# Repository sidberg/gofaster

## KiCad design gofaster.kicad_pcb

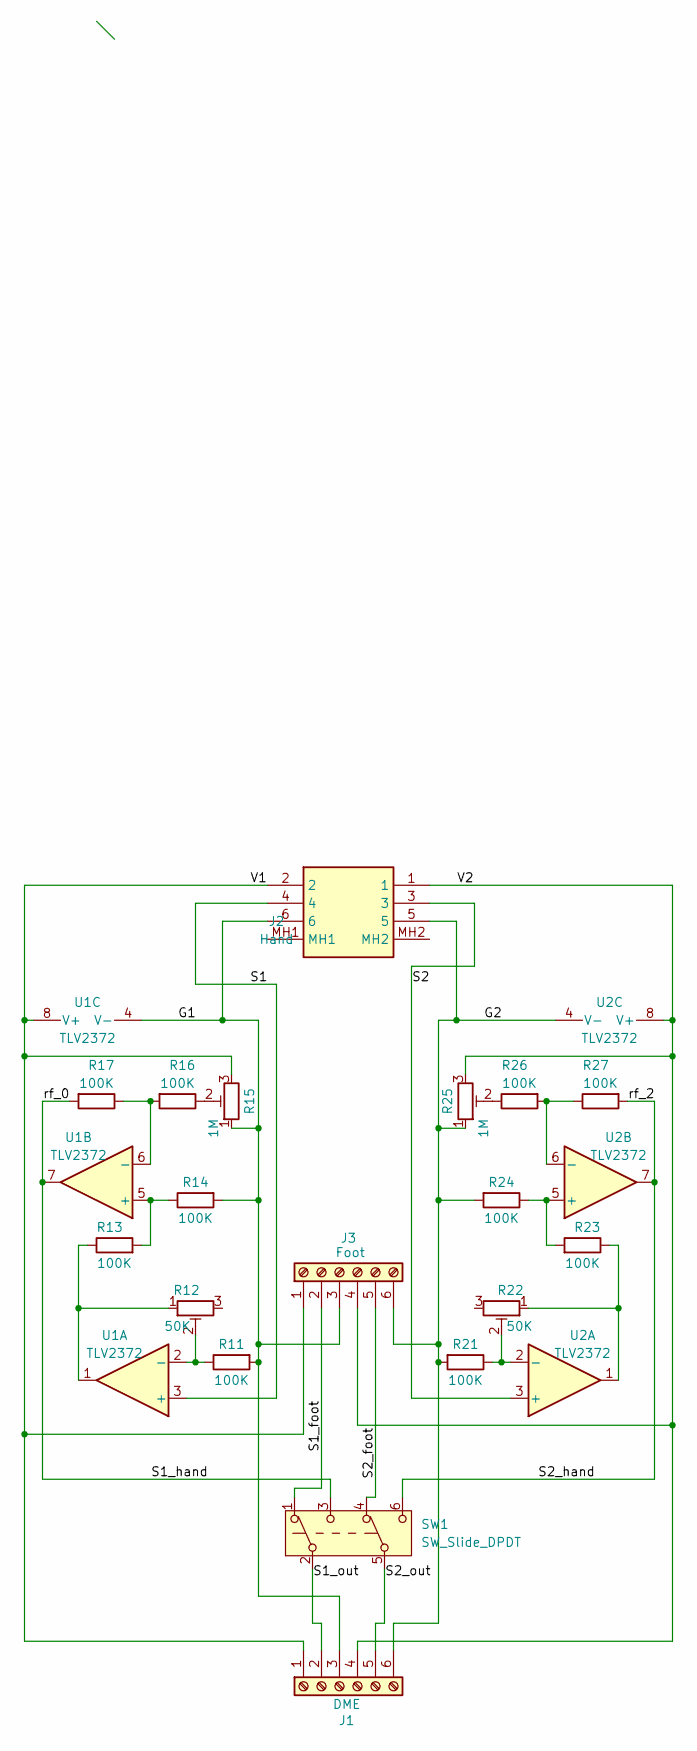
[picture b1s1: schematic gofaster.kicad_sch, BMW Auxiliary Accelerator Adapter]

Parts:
J1: DME; CUI_TB002-500-06BE
J2: Hand; 39294069; Mouser Part Number 538-39-29-4069
J3: Foot; CUI_TB002-500-06BE
R11, R13, R14, R16, R17, R21, R23, R24, R26, R27: 100K; R_Axial_DIN0207_L6.3mm_D2.5mm_P7.62mm_Horizontal
R12, R22: 50K; Potentiometer_Bourns_3339S_Horizontal
R15, R25: 1M; Potentiometer_Bourns_3339S_Horizontal
SW1: SW_Slide_DPDT; PBH2UEEKZXNAG1RBLK
U1, U2: TLV2372; DIP-8_W7.62mm

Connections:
/G1: J1.3, J2.6, J3.3, R11.2, R14.2, R15.1, U1.4 (V-)
/G2: J1.6, J2.5, J3.6, R21.2, R24.2, R25.1, U2.4 (V-)
/S1: J2.4, U1.3 (+)
/S1_foot: J3.2, SW1.1 (A)
/S1_hand: R17.2, SW1.3 (C), U1.7
/S1_out: J1.2, SW1.2 (B)
/S2: J2.3, U2.3 (+)
/S2_foot: J3.5, SW1.4 (A)
/S2_hand: R27.2, SW1.6 (C), U2.7
/S2_out: J1.5, SW1.5 (B)
/V1: J1.1, J2.2, J3.1, R15.3, U1.8 (V+)
/V2: J1.4, J2.1, J3.4, R25.3, U2.8 (V+)
unnamed: R12.1, R13.1, U1.1
unnamed: R15.2, R16.1
unnamed: R22.1, R23.1, U2.1
unnamed: R25.2, R26.1
unnamed: R11.1, R12.2, U1.2 (-)
unnamed: R13.2, R14.1, U1.5 (+)
unnamed: R16.2, R17.1, U1.6 (-)
unnamed: R21.1, R22.2, U2.2 (-)
unnamed: R23.2, R24.1, U2.5 (+)
unnamed: R26.2, R27.1, U2.6 (-)

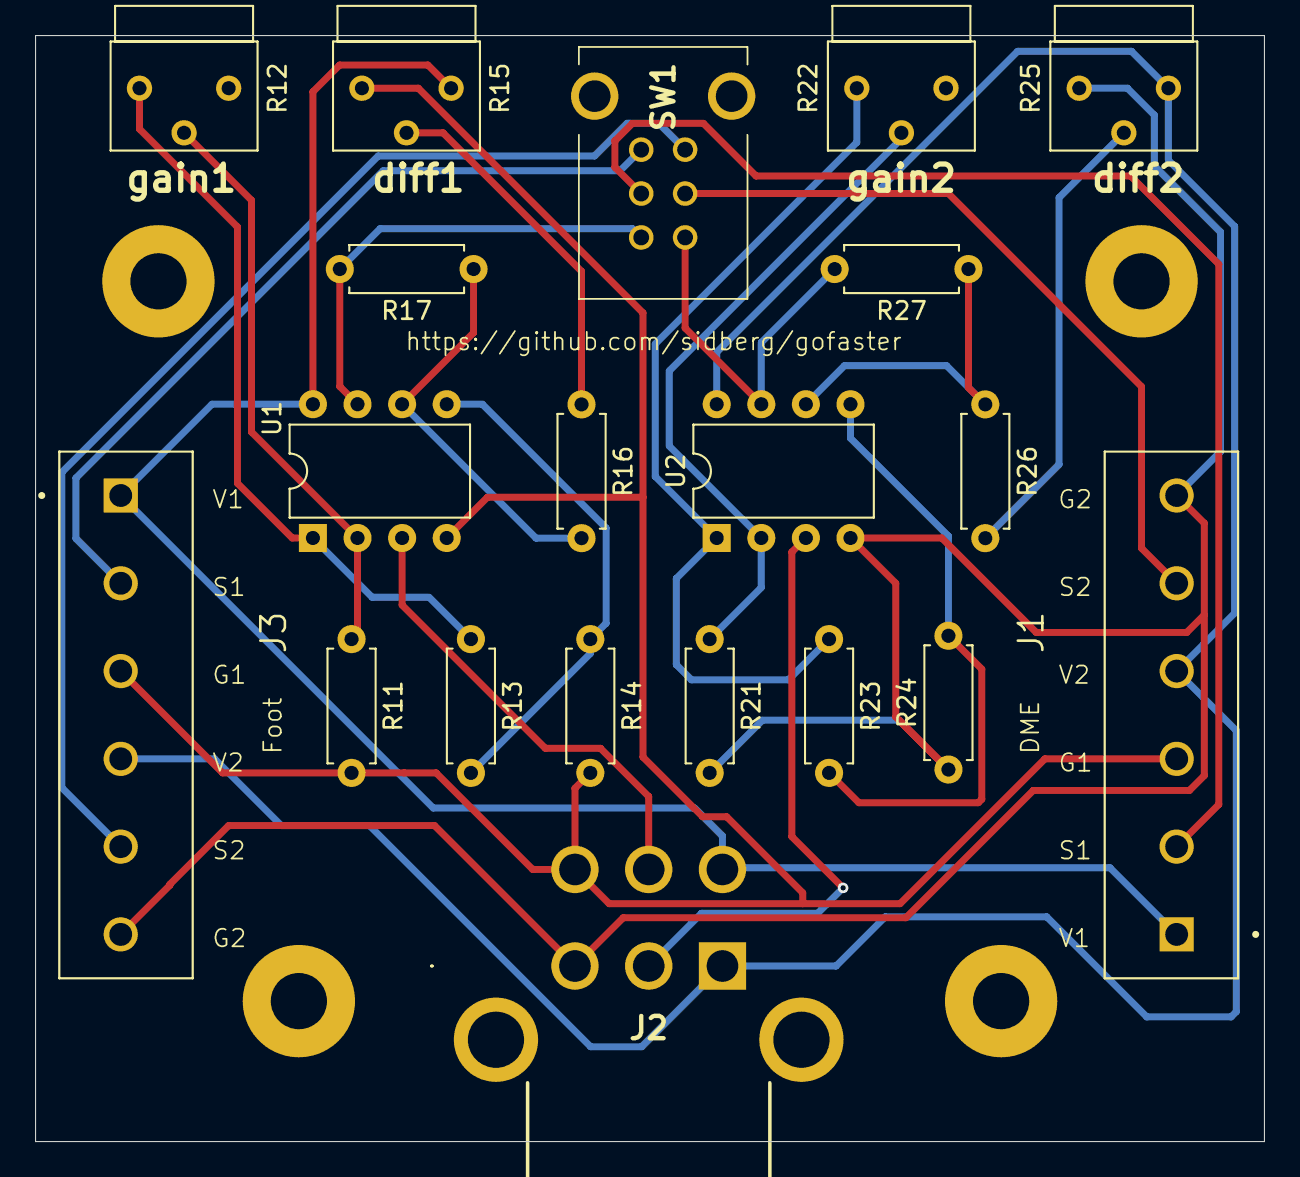
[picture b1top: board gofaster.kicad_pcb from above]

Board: 2 copper layers, 70.0 x 63.0 mm, 20 parts (0 on the bottom side), 22 nets.

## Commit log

2024-07-08 remove gerbers
2025-02-20 add enclosure
